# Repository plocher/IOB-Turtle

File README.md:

# IOB-Turtle
## License: CERN Open Hardware Licence v1.2

IOB Interface provides 1x IO4 port for connection to an IO4-Turtle

PNP Ready: IOB-Turtle - adapter for [IO4-Turtle](/pages/IO4-Turtle) controller and [I2C-7311](/pages/I2C-7311) IO expansion board

  * pin 1: 9-12vDC
  * pin 2: !DIVERGING - Turnout Position Feedback - low = Diverging, high = not diverging
  * pin 3: !NORMAL    - Turnout Position Feedback - low = Normal, high = not normal
  * pin 4: !OCCUPIED  - Detector - low = occupied, high = empty
  * pin 5: !MOTOR     - Motor Control Output - Low = Normal, High = Diverging
  * pin 6: GND

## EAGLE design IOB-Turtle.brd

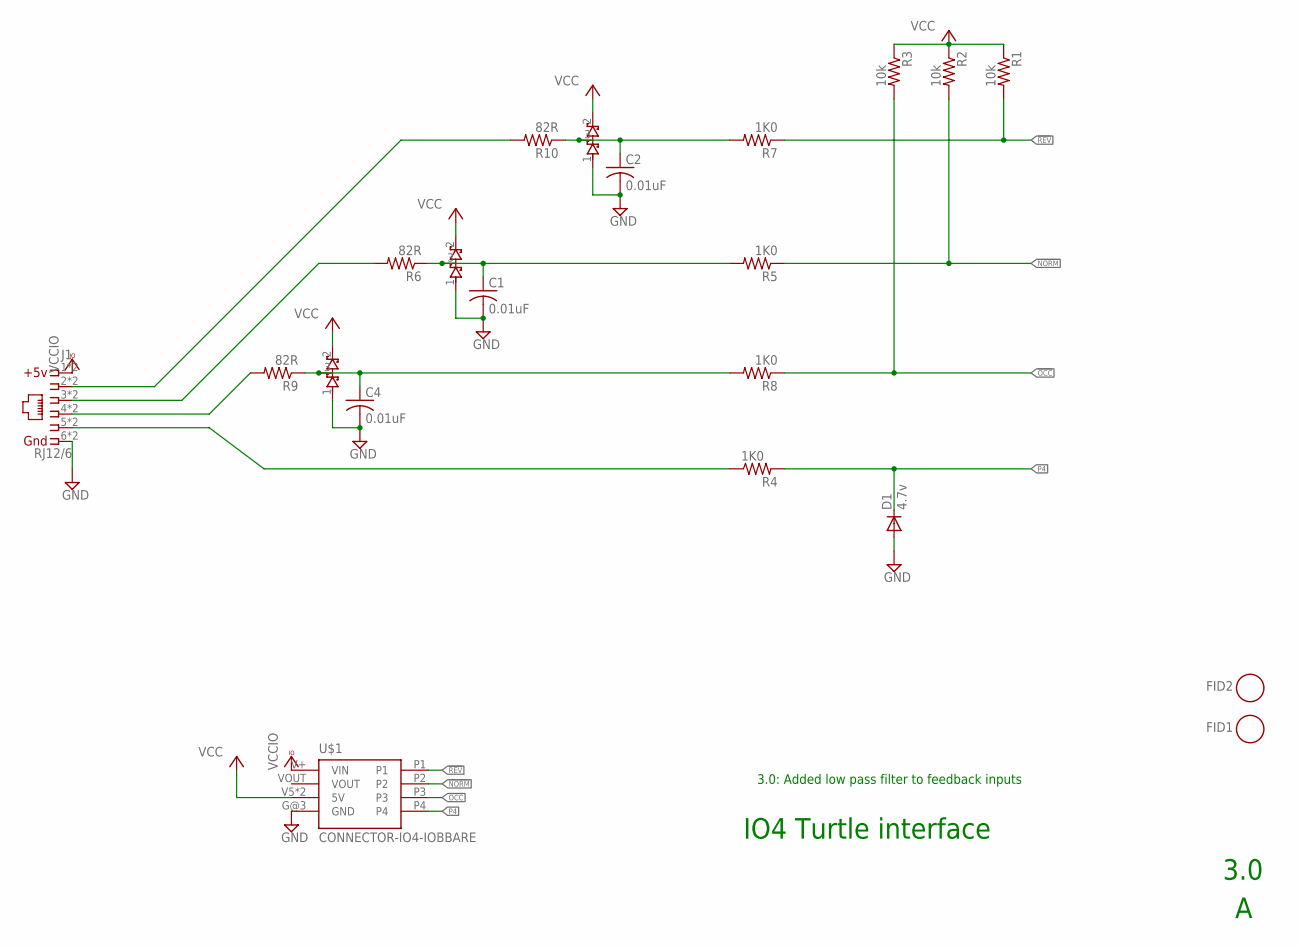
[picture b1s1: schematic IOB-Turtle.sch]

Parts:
C1, C2, C4: 0.01uF; 0603-CAP
D1: 4.7v; SOT23-3
D2, D3, D4: BAT54S; SOT23
FID1, FID2: FIDUCIAL; FIDUCIAL_1MM
J1: RJ12/6; RJ24-INVERTED-PINS
R1, R2, R3: 10k; 0805-RES
R4, R5, R7, R8: 1K0; 0603-RES
R6, R9, R10: 82R; 0805-RES
U$1: CONNECTOR-IO4-IOBBARE; IO4-IOB

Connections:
!NORM: R2.2, R5.1, U$1.P2
!OCC: R3.2, R8.1, U$1.P3
!REV: R1.2, R7.1, U$1.P1
GND: C1.2, C2.2, C4.2, D1.1 (A), D2.1 (A1), D3.1 (A1), D4.1 (A1), J1.6, J1.6@1 (6), U$1.G@3 (GND)
IO4-2: J1.2, J1.2@1 (2), R10.2
IO4-3: J1.3, J1.3@1 (3), R6.2
IO4-5: J1.5, J1.5@1 (5), R4.1
unnamed: J1.4, J1.4@1 (4), R9.2
unnamed: C1.1, D2.3 (COM), R5.2, R6.1
unnamed: C2.1, D3.3 (COM), R7.2, R10.1
unnamed: C4.1, D4.3 (COM), R8.2, R9.1
P4: D1.3 (C), R4.2, U$1.P4
VCC: D2.2 (C2), D3.2 (C2), D4.2 (C2), R1.1, R2.1, R3.1, U$1.V5 (5V), U$1.V5@1 (5V)
VCCIO: J1.1, J1.1@1 (1), U$1.V+ (VIN)

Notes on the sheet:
IO4 Turtle interface
3.0
3.0: Added low pass filter to feedback inputs

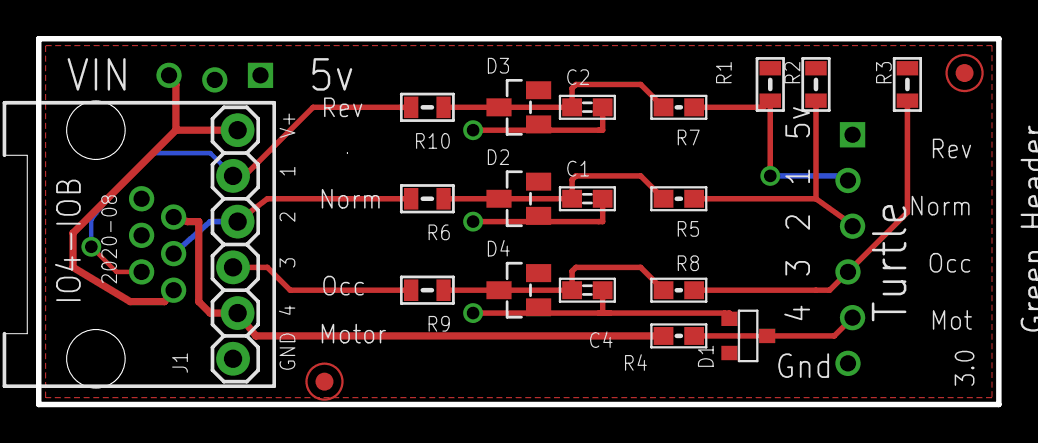
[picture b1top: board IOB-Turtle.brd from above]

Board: 2 copper layers, 53.3 x 20.3 mm, 21 parts (0 on the bottom side), 14 nets.

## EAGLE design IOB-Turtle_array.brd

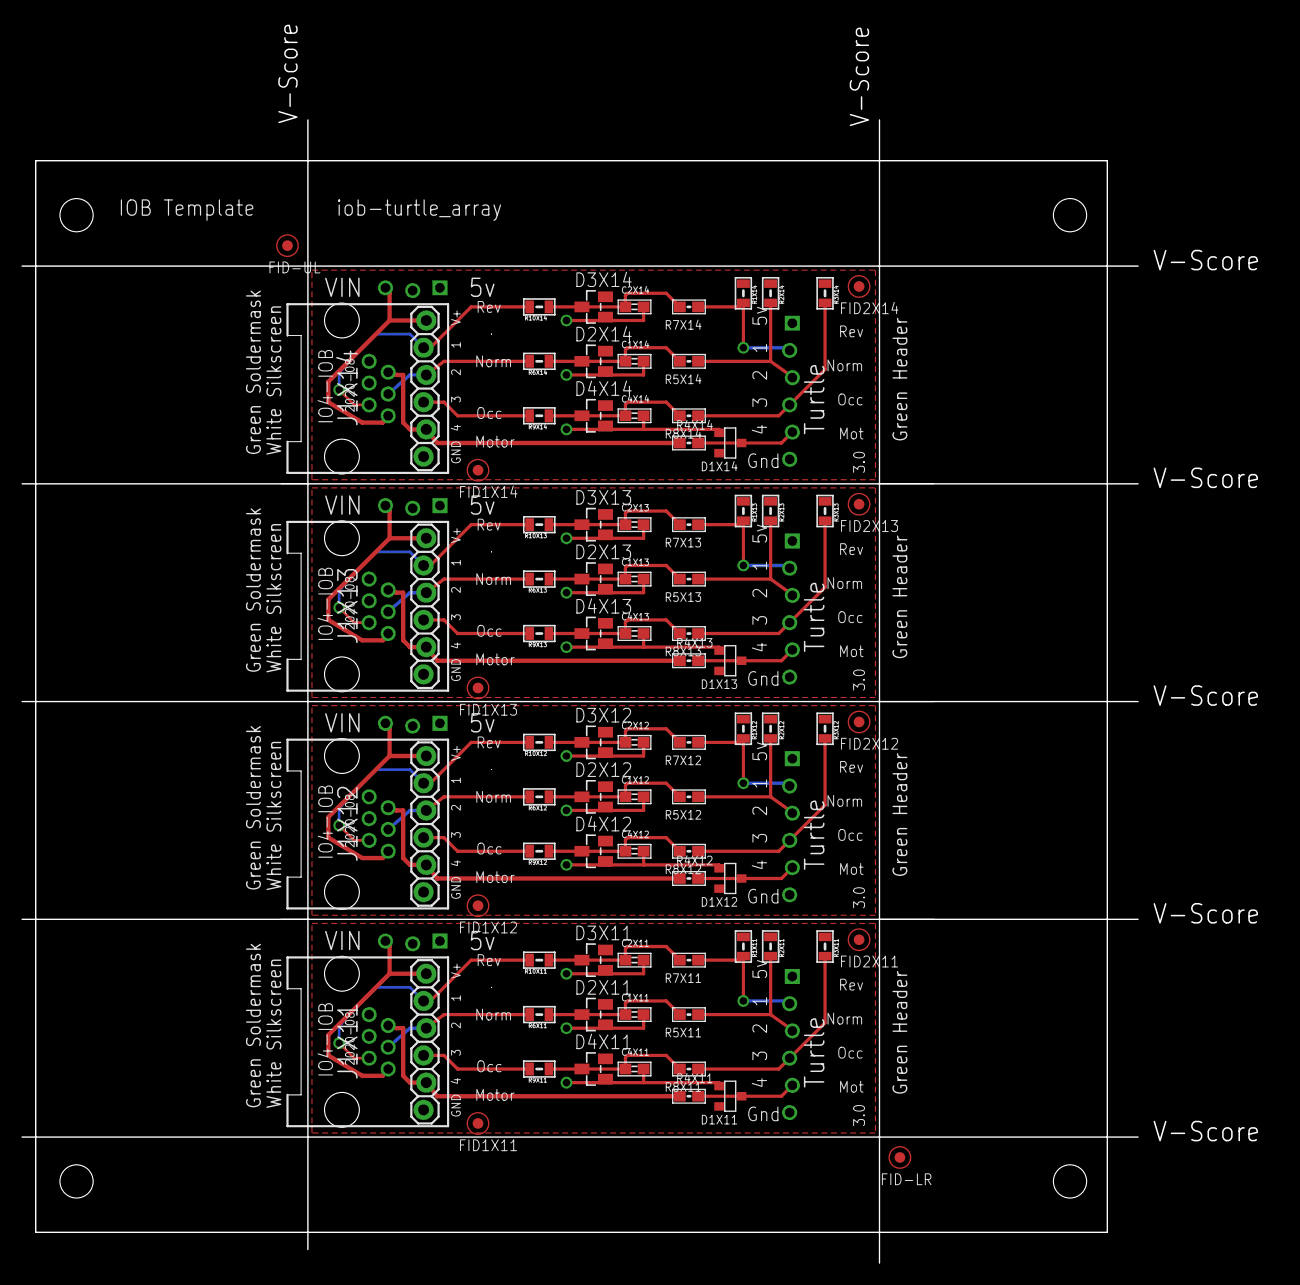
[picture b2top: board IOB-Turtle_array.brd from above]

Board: 2 copper layers, 117.2 x 115.8 mm, 87 parts (0 on the bottom side), 56 nets.

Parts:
C1X11, C1X12, C1X13, C1X14, C2X11, C2X12, C2X13, C2X14, C4X11, C4X12, C4X13, C4X14: 0.01uF; 0603-CAP
D1X11, D1X12, D1X13, D1X14: 4.7v; SOT23-3
D2X11, D2X12, D2X13, D2X14, D3X11, D3X12, D3X13, D3X14, D4X11, D4X12, D4X13, D4X14: BAT54S; SOT23
FID1X11, FID1X12, FID1X13, FID1X14, FID2X11, FID2X12, FID2X13, FID2X14: FIDUCIAL; FIDUCIAL_1MM
FID-LR: FIDUCIAL; FIDUCIAL_1MM
FID-UL: FIDUCIAL; FIDUCIAL_1MM
J1X11, J1X12, J1X13, J1X14: RJ12/6; RJ24-INVERTED-PINS
R1X11, R1X12, R1X13, R1X14, R2X11, R2X12, R2X13, R2X14, R3X11, R3X12, R3X13, R3X14: 10k; 0805-RES
R4X11, R4X12, R4X13, R4X14, R5X11, R5X12, R5X13, R5X14, R7X11, R7X12, R7X13, R7X14, R8X11, R8X12, R8X13, R8X14: 1K0; 0603-RES
R6X11, R6X12, R6X13, R6X14, R9X11, R9X12, R9X13, R9X14, R10X11, R10X12, R10X13, R10X14: 82R; 0805-RES
U$1X1: BOARD-DINRAIL-3.17IN-H4X-IOB
U$1X11, U$1X12, U$1X13, U$1X14: CONNECTOR-IO4-IOBBARE; IO4-IOB

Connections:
!NORMX11: R2X11.2, R5X11.1, U$1X11.P2
!NORMX12: R2X12.2, R5X12.1, U$1X12.P2
!NORMX13: R2X13.2, R5X13.1, U$1X13.P2
!NORMX14: R2X14.2, R5X14.1, U$1X14.P2
!OCCX11: R3X11.2, R8X11.1, U$1X11.P3
!OCCX12: R3X12.2, R8X12.1, U$1X12.P3
!OCCX13: R3X13.2, R8X13.1, U$1X13.P3
!OCCX14: R3X14.2, R8X14.1, U$1X14.P3
!REVX11: R1X11.2, R7X11.1, U$1X11.P1
!REVX12: R1X12.2, R7X12.1, U$1X12.P1
!REVX13: R1X13.2, R7X13.1, U$1X13.P1
!REVX14: R1X14.2, R7X14.1, U$1X14.P1
GNDX11: C1X11.2, C2X11.2, C4X11.2, D1X11.1, D2X11.1, D3X11.1, D4X11.1, J1X11.6, J1X11.6@1, U$1X11.G@3
GNDX12: C1X12.2, C2X12.2, C4X12.2, D1X12.1, D2X12.1, D3X12.1, D4X12.1, J1X12.6, J1X12.6@1, U$1X12.G@3
GNDX13: C1X13.2, C2X13.2, C4X13.2, D1X13.1, D2X13.1, D3X13.1, D4X13.1, J1X13.6, J1X13.6@1, U$1X13.G@3
GNDX14: C1X14.2, C2X14.2, C4X14.2, D1X14.1, D2X14.1, D3X14.1, D4X14.1, J1X14.6, J1X14.6@1, U$1X14.G@3
IO4-2X11: J1X11.2, J1X11.2@1, R10X11.2
IO4-2X12: J1X12.2, J1X12.2@1, R10X12.2
IO4-2X13: J1X13.2, J1X13.2@1, R10X13.2
IO4-2X14: J1X14.2, J1X14.2@1, R10X14.2
IO4-3X11: J1X11.3, J1X11.3@1, R6X11.2
IO4-3X12: J1X12.3, J1X12.3@1, R6X12.2
IO4-3X13: J1X13.3, J1X13.3@1, R6X13.2
IO4-3X14: J1X14.3, J1X14.3@1, R6X14.2
IO4-5X11: J1X11.5, J1X11.5@1, R4X11.1
IO4-5X12: J1X12.5, J1X12.5@1, R4X12.1
IO4-5X13: J1X13.5, J1X13.5@1, R4X13.1
IO4-5X14: J1X14.5, J1X14.5@1, R4X14.1
unnamed: J1X11.4, J1X11.4@1, R9X11.2
unnamed: J1X12.4, J1X12.4@1, R9X12.2
unnamed: J1X13.4, J1X13.4@1, R9X13.2
unnamed: J1X14.4, J1X14.4@1, R9X14.2
unnamed: C1X11.1, D2X11.3, R5X11.2, R6X11.1
unnamed: C1X12.1, D2X12.3, R5X12.2, R6X12.1
unnamed: C1X13.1, D2X13.3, R5X13.2, R6X13.1
unnamed: C1X14.1, D2X14.3, R5X14.2, R6X14.1
unnamed: C2X11.1, D3X11.3, R7X11.2, R10X11.1
unnamed: C2X12.1, D3X12.3, R7X12.2, R10X12.1
unnamed: C2X13.1, D3X13.3, R7X13.2, R10X13.1
unnamed: C2X14.1, D3X14.3, R7X14.2, R10X14.1
unnamed: C4X11.1, D4X11.3, R8X11.2, R9X11.1
unnamed: C4X12.1, D4X12.3, R8X12.2, R9X12.1
unnamed: C4X13.1, D4X13.3, R8X13.2, R9X13.1
unnamed: C4X14.1, D4X14.3, R8X14.2, R9X14.1
P4X11: D1X11.3, R4X11.2, U$1X11.P4
P4X12: D1X12.3, R4X12.2, U$1X12.P4
P4X13: D1X13.3, R4X13.2, U$1X13.P4
P4X14: D1X14.3, R4X14.2, U$1X14.P4
VCCIOX11: J1X11.1, J1X11.1@1, U$1X11.V+
VCCIOX12: J1X12.1, J1X12.1@1, U$1X12.V+
VCCIOX13: J1X13.1, J1X13.1@1, U$1X13.V+
VCCIOX14: J1X14.1, J1X14.1@1, U$1X14.V+
VCCX11: D2X11.2, D3X11.2, D4X11.2, R1X11.1, R2X11.1, R3X11.1, U$1X11.V5, U$1X11.V5@1
VCCX12: D2X12.2, D3X12.2, D4X12.2, R1X12.1, R2X12.1, R3X12.1, U$1X12.V5, U$1X12.V5@1
VCCX13: D2X13.2, D3X13.2, D4X13.2, R1X13.1, R2X13.1, R3X13.1, U$1X13.V5, U$1X13.V5@1
VCCX14: D2X14.2, D3X14.2, D4X14.2, R1X14.1, R2X14.1, R3X14.1, U$1X14.V5, U$1X14.V5@1

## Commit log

2019-12-09 added graphic
2020-03-06 Version 2.0
2020-03-06 text should be on tPlace, not tDocu
2020-05-04 updated tags
2020-08-09 fixed SPCoast.lbr orientation
2020-08-09 Added missing values
2020-08-11 add lpf on inputs, normalized silkscreen layout across IOBs
2020-08-11 bottom silk alignment
